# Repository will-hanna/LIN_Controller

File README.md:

# LIN_Controller
LIN Controller
KiCad files

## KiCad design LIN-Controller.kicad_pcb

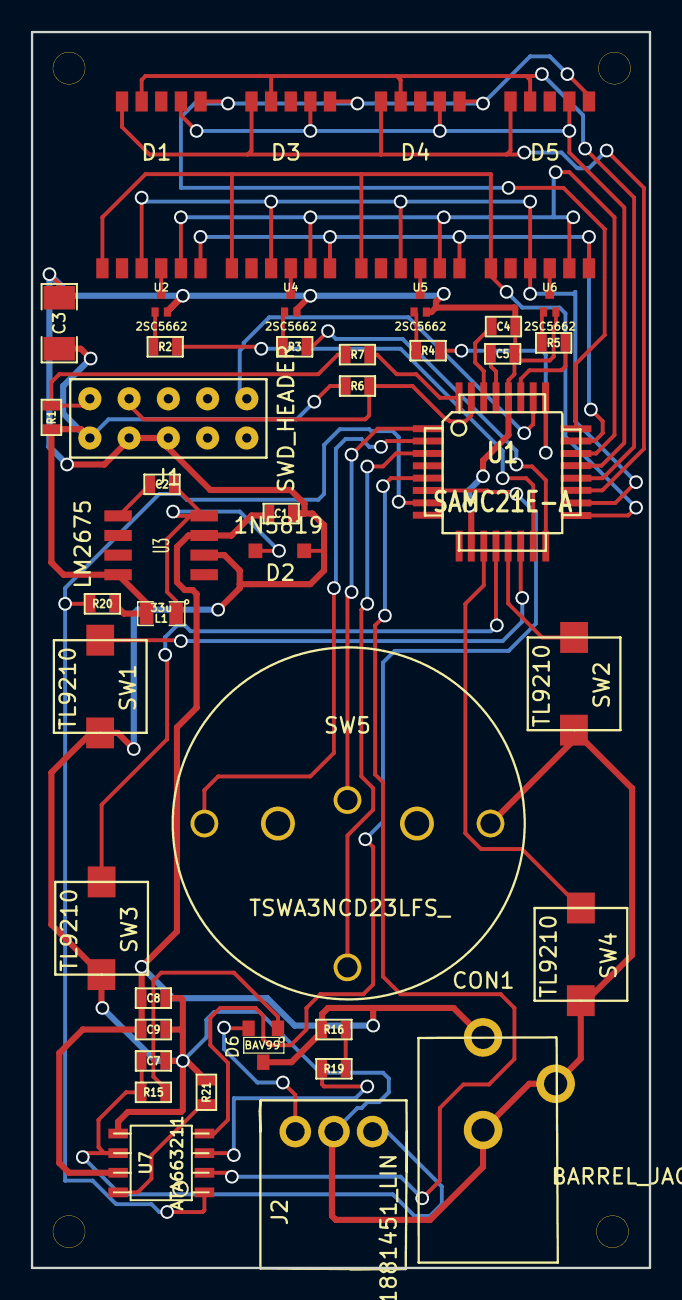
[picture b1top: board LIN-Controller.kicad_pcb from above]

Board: 2 copper layers, 40.0 x 80.0 mm, 42 parts (0 on the bottom side), 43 nets.

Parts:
C1: 47u; SM0603
C2, C4, C5, C8: 0.1u; SM0603
C3: 100u; SM1206
C7: 220p; SM0603
C9: 10u; SM0603
CON1: BARREL_JACK; PJ-002A
D1, D3, D4, D5: HDSM-283L; HDSM-283
D2: 1N5819; SOD123
D6: BAV99; SOT23
J1: SWD_HEADER; SWD Header
J2: 1881451_LIN; 1881451
L1: 33u; SM0805
R1, R6, R16: 10K; SM0603
R2, R3, R4, R5: 330R; SM0603
R7: 22R; SM0603
R15: 1K; SM0603
R19: 2.7K; SM0603
R20: 4K7; SM0603
R21: 100K; SM0603
SW1, SW2, SW3, SW4: TL9210
SW5: TSWA3NCD23LFS_; TSWA3NCD23LFS
U1: SAMC21E-A; TQFP32
U2, U4, U5, U6: 2SC5662; SOT723
U3: LM2675; SOIC8-narrow
U7: ATA663211; so-8

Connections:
3V3: C3.1, J1.1, L1.2, R1.1, R6.1, R20.1, U3.4
/DIS'.': D1.7, D3.7, D4.7, D5.7, U1.24
/DIS'a': D1.6, D3.6, D4.6, D5.6, U1.23
/DIS'b': D1.5, D3.5, D4.5, D5.5, U1.22
/DIS'c': D1.8, D3.8, D4.8, D5.8, U1.21
/DIS'd': D1.10, D3.10, D4.10, D5.10, U1.20
/DIS'e': D1.11, D3.11, D4.11, D5.11, U1.19
/DIS'f': D1.3, D3.3, D4.3, D5.3, U1.18
/DIS'g': D1.1, D3.1, D4.1, D5.1, U1.17
/DS0: R5.1, U1.27
/DS1: R4.1, U1.25
/DS2: R3.1, U1.16
/DS3: R2.1, U1.15
/EN: U1.5, U7.2
/PB0: SW1.2, U1.14
/PB1: SW2.2, U1.13
/PB2: SW3.2, U1.12
/PB3: SW4.2, U1.11
/RXD: R20.2, U1.7, U7.1
/TWA: SW5.1, U1.2
/TWB: SW5.2, U1.3
/TWC: SW5.3, U1.1
/TXD: U1.6, U7.4
GND: C1.2, C3.2, C4.2, C5.2, C7.2, C8.2, C9.2, CON1.2, CON1.3, D2.1, J1.3, J1.5, J2.2, R21.2, SW1.1, SW2.1, SW3.1, SW4.1, SW5.4, U1.10, U1.28, U2.2, U3.6, U4.2, U5.2, U6.2, U7.5
unnamed: C2.1, U3.1
unnamed: C2.2, D2.2, L1.1, U3.8
unnamed: C4.1, U1.30
unnamed: C5.1, U1.29
unnamed: C7.1, J2.3, R15.1, U7.6
unnamed: D6.1, R15.2
unnamed: D6.2, J2.1
unnamed: J1.2, R1.2, R7.2
unnamed: J1.4, R6.2, U1.31
unnamed: J1.10, U1.26
unnamed: R2.2, U2.1
unnamed: R3.2, U4.1
unnamed: R4.2, U5.1
unnamed: R5.2, U6.1
unnamed: R7.1, U1.32
unnamed: R16.2, R19.1
unnamed: R19.2, U7.3
unnamed: R21.1, U7.8
VsLIN: C1.1, C8.1, C9.1, CON1.1, D6.3, R16.1, U3.7, U7.7

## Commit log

2016-03-28 Added files via upload
